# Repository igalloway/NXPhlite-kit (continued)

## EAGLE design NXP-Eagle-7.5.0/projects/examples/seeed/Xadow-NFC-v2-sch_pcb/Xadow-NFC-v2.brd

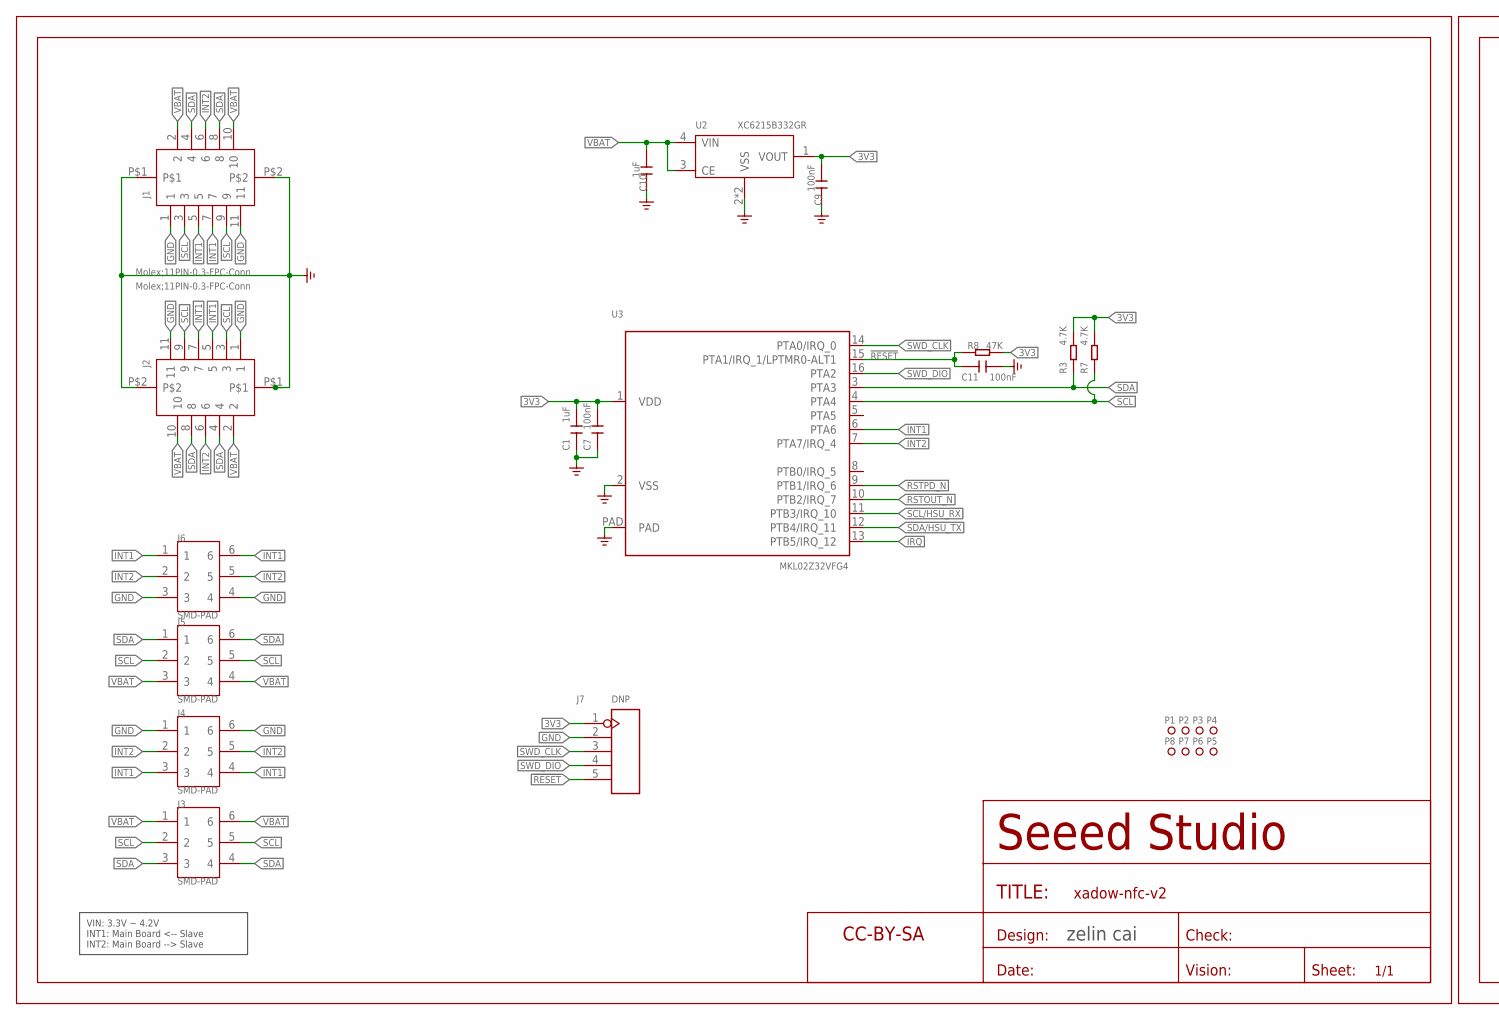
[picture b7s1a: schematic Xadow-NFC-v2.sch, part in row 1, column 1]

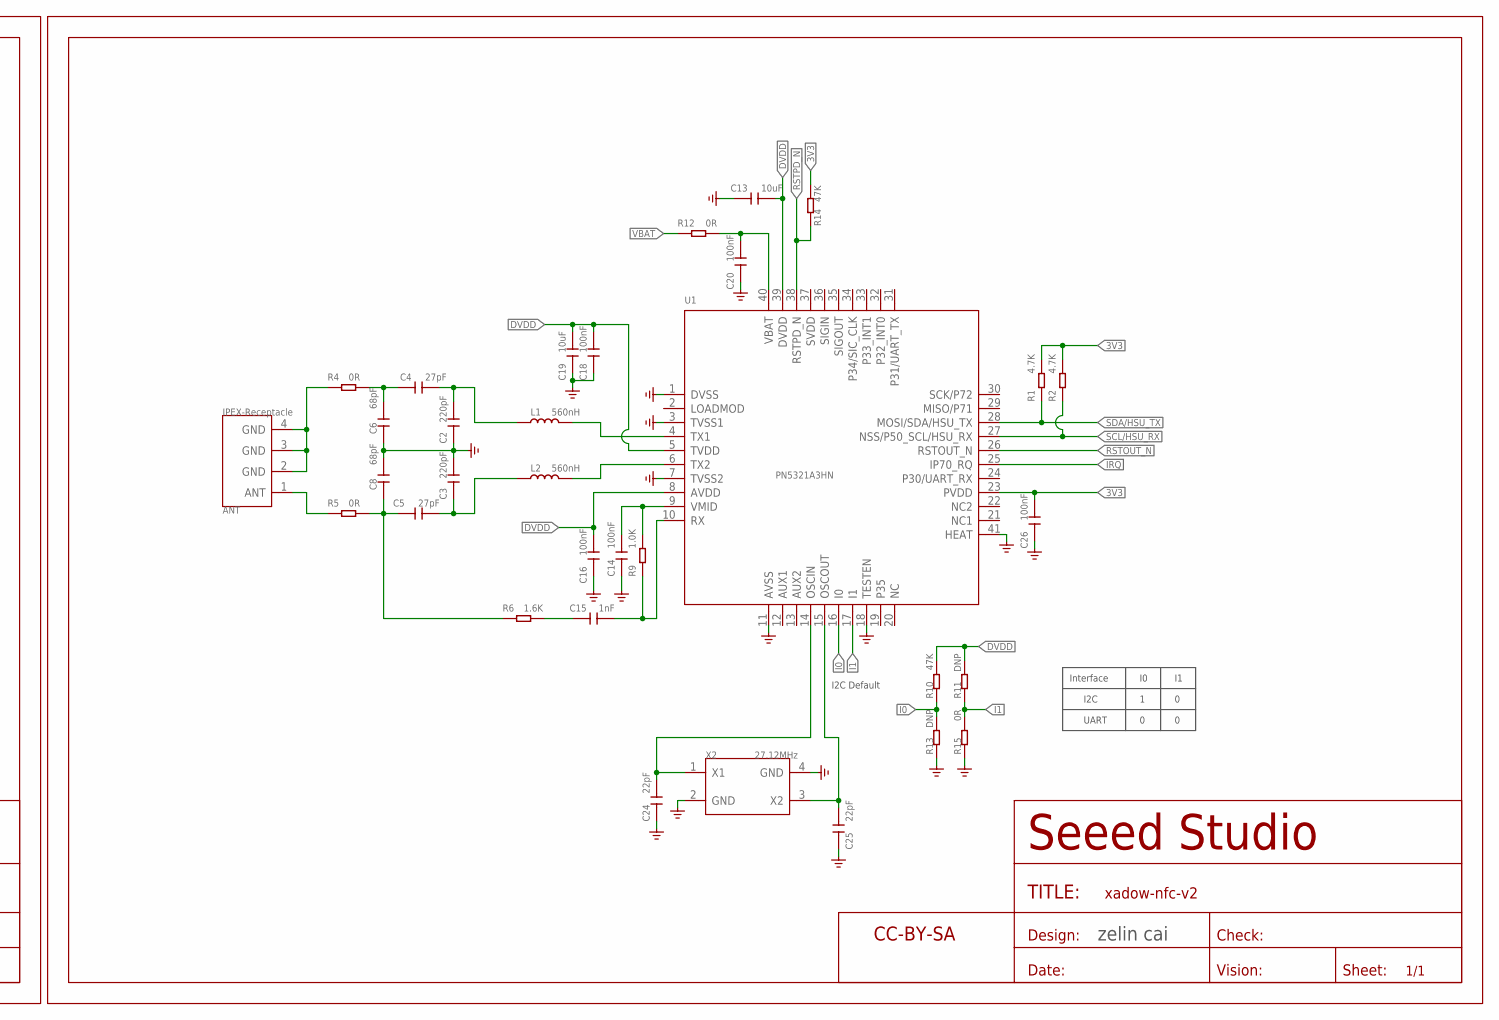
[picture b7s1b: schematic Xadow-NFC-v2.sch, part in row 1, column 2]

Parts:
ANT: IPEX-Receptacle; ANT-IPEX4-1.7X1.7MM
C1, C10: 1uF; C0402
C2, C3: 220pF; C0402
C4, C5: 27pF; C0402
C6, C8: 68pF; C0402
C7, C9, C11, C14, C16, C18, C20, C26: 100nF; C0402
C13, C19: 10uF; C0402
C15: 1nF; C0402
C24, C25: 22pF; C0402
J1, J2: Molex;11PIN-0.3-FPC-Conn; FPC11-SMD-0.3(FH35C)
J3: SMD-PAD; 6P-DIP-2_S3
J4, J6: SMD-PAD; 6P-DIP-2_ROUND
J5: SMD-PAD; 6P-DIP-2
J7: DNP; H5-SMD-2.0-TEST
L1, L2: 560nH; L0603
P1, P2, P3, P4, P5, P6, P7, P8: MRK; ROUND-MARK-1.0
R1, R2, R3, R7: 4.7K; R0402
R4, R5, R12, R15: 0R; R0402
R6: 1.6K; R0402
R8, R10, R14: 47K; R0402
R9: 1.0K; R0402
R11, R13: DNP; R0402
U1: PN5321A3HN; QFN40G-0.5-6X6MM
U2: XC6215B332GR; USP4-0.6-1.2X1.6MM
U3: MKL02Z32VFG4; QFN16G-0.5-3X3MM
U$1: PAGE1; SEEEDSTUDIO-PCB-FRAME
U$21: PAGE2; SEEEDSTUDIO-PCB-FRAME
X2: 27.12MHz; SMD4P-2.0X1.6X0.5MM

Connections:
3V3: C1.2, C7.2, C9.2, C26.2, J7.1, R1.2, R2.2, R3.2, R7.2, R8.2, R14.2, U1.23 (PVDD), U2.1 (VOUT), U3.1 (VDD)
!RESET: C11.1, J7.5, R8.1, U3.15 (PTA1/IRQ_1/LPTMR0-ALT1)
DVDD: C13.1, C16.2, C18.2, C19.2, R10.1, R11.1, U1.5 (TVDD), U1.8 (AVDD), U1.39 (DVDD)
GND: C1.1, C2.1, C3.2, C6.2, C7.1, C8.1, C9.1, C10.1, C11.2, C13.2, C14.1, C16.1, C18.1, C19.1, C20.1, C24.1, C25.1, C26.1, J1.1, J1.11, J1.P$1, J1.P$2, J2.1, J2.11, J2.P$1, J2.P$2, J4.1, J4.6, J6.3, J6.4, J7.2, R13.2, R15.2, U1.1 (DVSS), U1.3 (TVSS1), U1.7 (TVSS2), U1.11 (AVSS), U1.18 (TESTEN), U1.41 (HEAT), U2.2 (VSS), U2.PAD (VSS), U3.2 (VSS), U3.PAD, X2.2 (GND), X2.4 (GND)
I0: R10.2, R13.1, U1.16 (I0)
I1: R11.2, R15.1, U1.17 (I1)
INT1: J1.5, J1.7, J2.5, J2.7, J4.3, J4.4, J6.1, J6.6, U3.6 (PTA6)
INT2: J1.6, J2.6, J4.2, J4.5, J6.2, J6.5, U3.7 (PTA7/IRQ_4)
IRQ: U1.25 (IP70_RQ), U3.13 (PTB5/IRQ_12)
unnamed: C15.1, R9.1, U1.10 (RX)
unnamed: C14.2, R9.2, U1.9 (VMID)
unnamed: C3.1, C5.1, L2.1
unnamed: C2.2, C4.1, L1.1
unnamed: C4.2, C6.1, R4.2
unnamed: C5.2, C8.2, R5.2, R6.1
unnamed: ANT.2 (GND), ANT.3 (GND), ANT.4 (GND), R4.1
unnamed: ANT.1 (ANT), R5.1
unnamed: C15.2, R6.2
unnamed: C24.2, U1.14 (OSCIN), X2.1 (X1)
unnamed: C25.2, U1.15 (OSCOUT), X2.3 (X2)
RSTOUT_N: U1.26 (RSTOUT_N), U3.10 (PTB2/IRQ_7)
RSTPD_N: R14.1, U1.38 (RSTPD_N), U3.9 (PTB1/IRQ_6)
SCL: J1.3, J1.9, J2.3, J2.9, J3.2, J3.5, J5.2, J5.5, R7.1, U3.4 (PTA4)
SCL/HSU_RX: R2.1, U1.27 (NSS/P50_SCL/HSU_RX), U3.11 (PTB3/IRQ_10)
SDA: J1.4, J1.8, J2.4, J2.8, J3.3, J3.4, J5.1, J5.6, R3.1, U3.3 (PTA3)
SDA/HSU_TX: R1.1, U1.28 (MOSI/SDA/HSU_TX), U3.12 (PTB4/IRQ_11)
SWD_CLK: J7.3, U3.14 (PTA0/IRQ_0)
SWD_DIO: J7.4, U3.16 (PTA2)
TX_N: L1.2, U1.4 (TX1)
TX_P: L2.2, U1.6 (TX2)
VBAT: C10.2, C20.2, J1.2, J1.10, J2.2, J2.10, J3.1, J3.6, J5.3, J5.4, R12.1, R12.2, U1.40 (VBAT), U2.3 (CE), U2.4 (VIN)

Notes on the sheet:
zelin cai
VIN: 3.3V ~ 4.2V INT1: Main Board <-- Slave INT2: Main Board --> Slave
Interface
I2C
UART
I2C Default

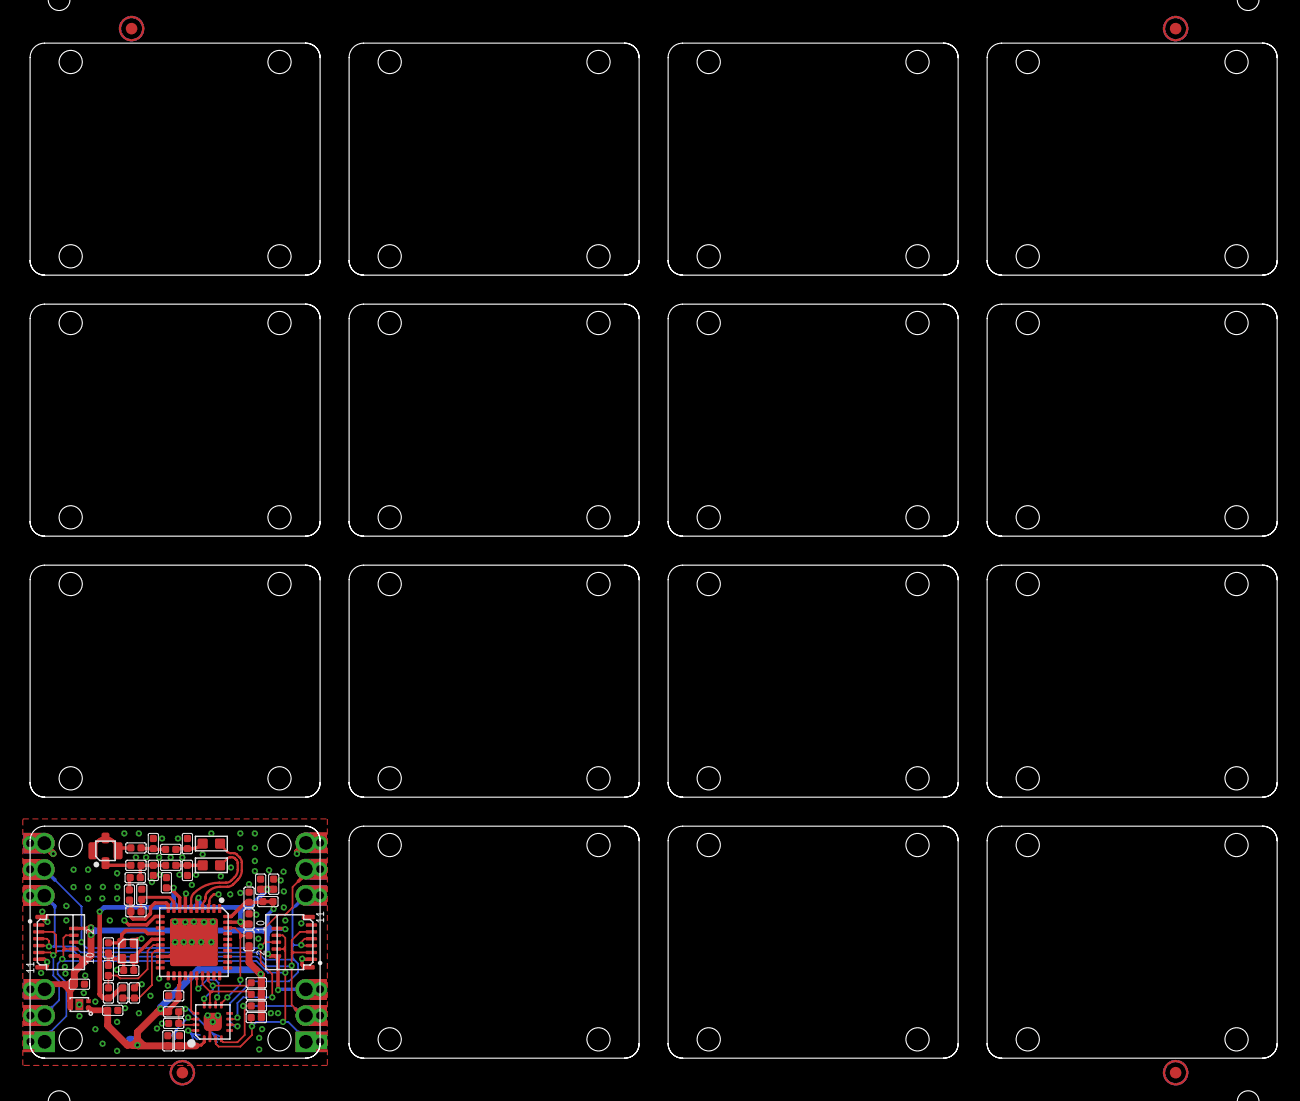
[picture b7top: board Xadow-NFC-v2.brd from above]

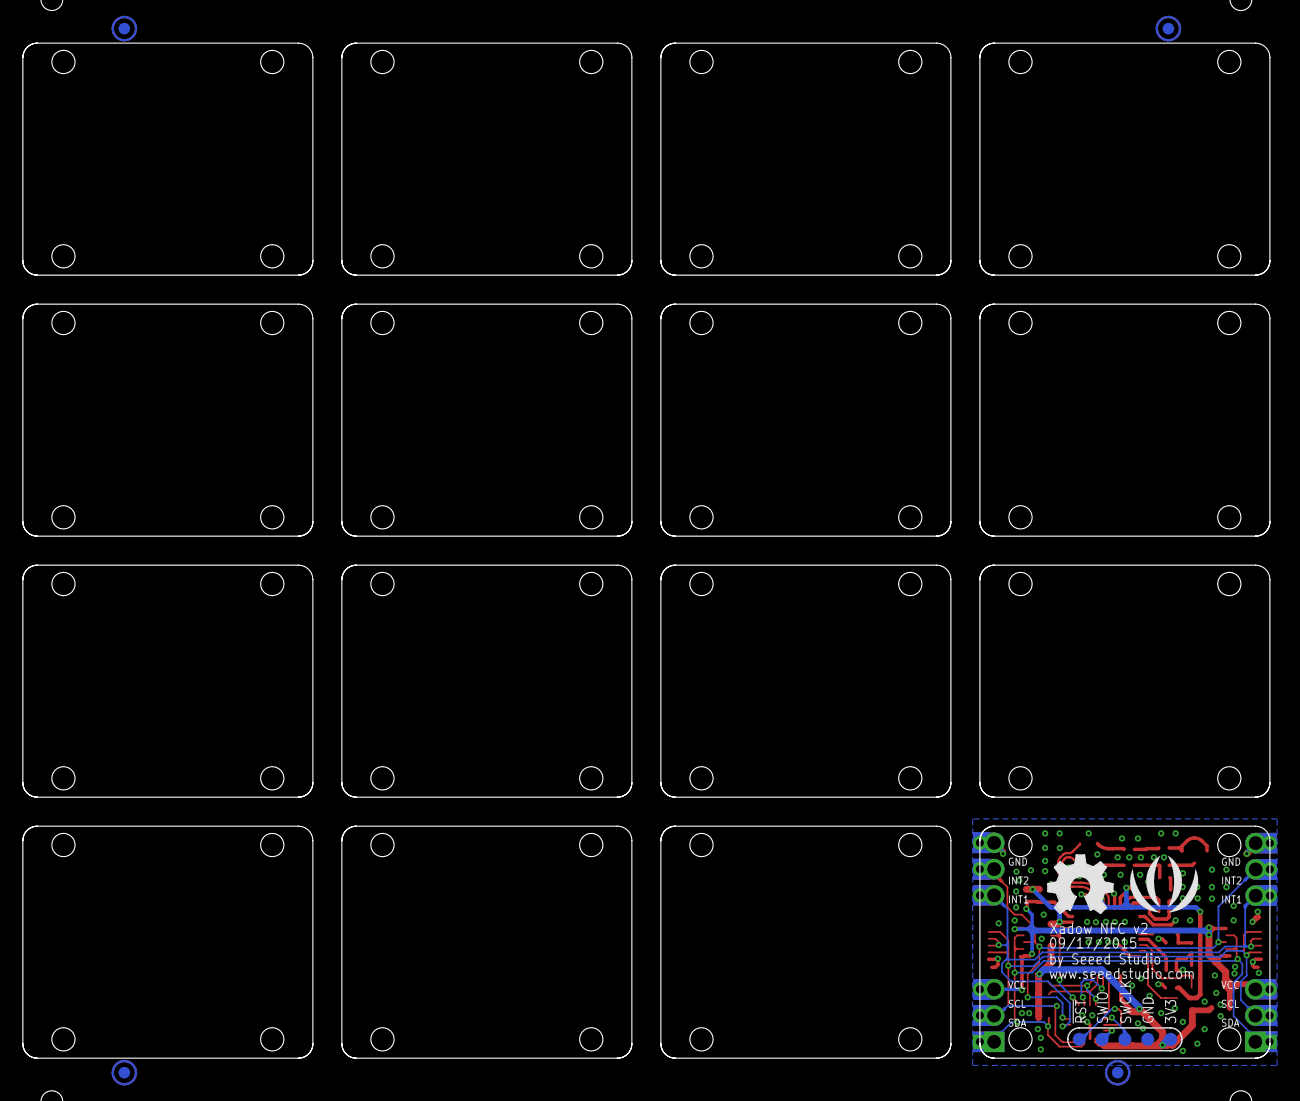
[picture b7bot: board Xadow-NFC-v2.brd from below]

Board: 2 copper layers, 109.2 x 88.9 mm, 62 parts (7 on the bottom side), 31 nets.

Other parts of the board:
U$27: OSHW_FILLX200_NOTEXT
U$29: SEEED-SILK-280*268MIL

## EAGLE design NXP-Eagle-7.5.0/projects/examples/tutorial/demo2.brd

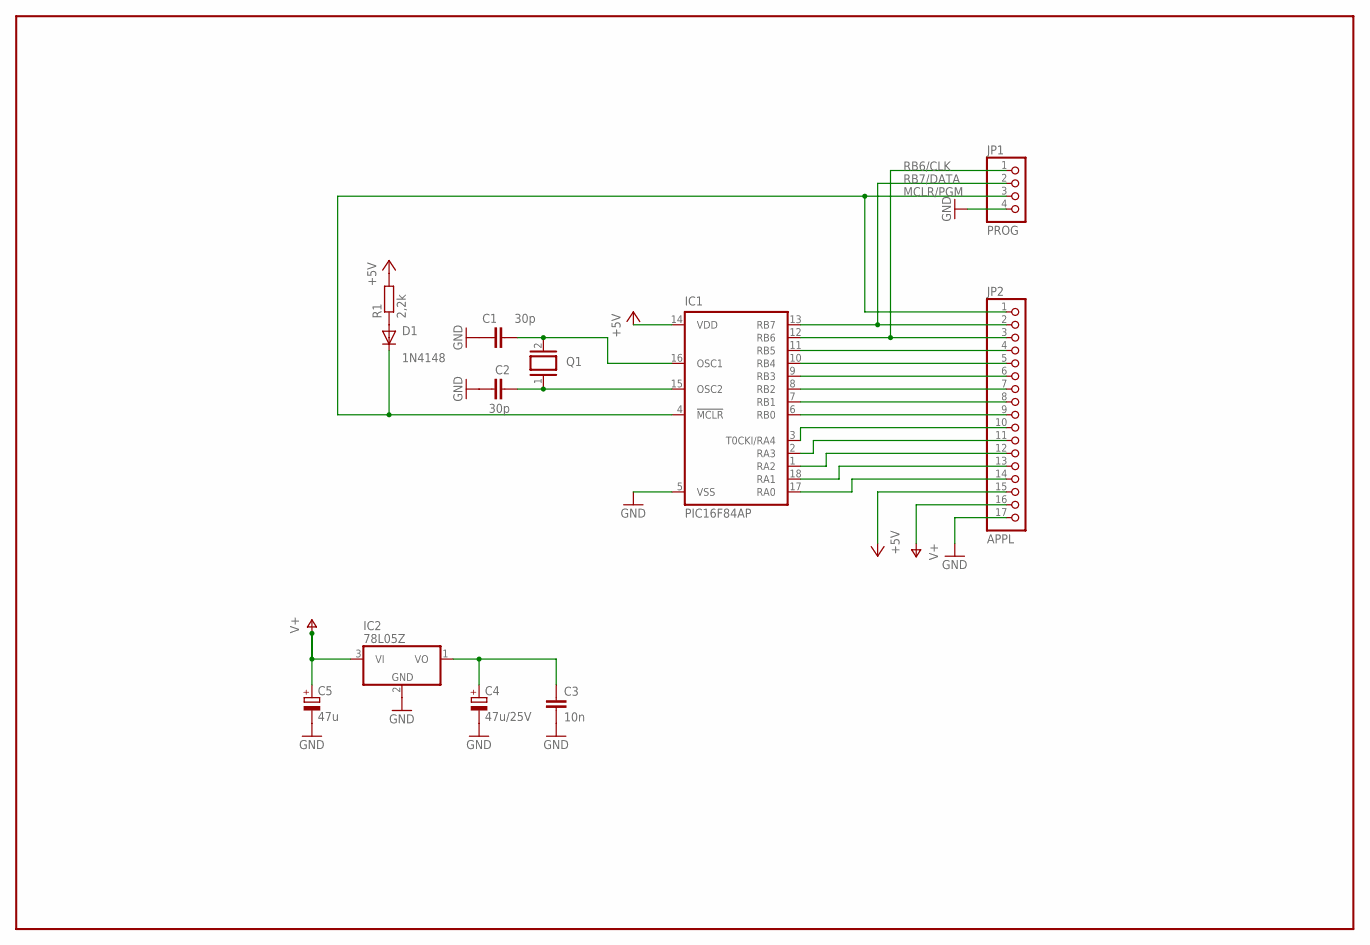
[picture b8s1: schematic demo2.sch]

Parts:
C1, C2: 30p; C1206
C3: 10n; C025-025X050
C4: 47u/25V; TAP5-45
C5: 47u; TAP5-45
D1: 1N4148; DO35-10
IC1: PIC16F84AP; DIL18
IC2: 78L05Z; TO92
JP1: PROG; 1X04
JP2: APPL; 1X17
Q1: XTAL/S; QS
R1: 2,2k; R1206

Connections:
+5V: IC1.14 (VDD), JP2.15, R1.1 (2)
GND: C1.1, C2.1, C3.2, C4.-, C5.-, IC1.5 (VSS), IC2.2 (GND), JP1.4, JP2.17
MCLR/PGM: D1.C, IC1.4 (!MCLR), JP1.3, JP2.1
unnamed: C3.1, C4.+, IC2.1 (VO)
unnamed: C1.2, IC1.16 (OSC1), Q1.2
unnamed: C2.2, IC1.15 (OSC2), Q1.1
unnamed: D1.A, R1.2 (1)
RA0: IC1.17 (RA0), JP2.14
RA1: IC1.18 (RA1), JP2.13
RA2: IC1.1 (RA2), JP2.12
RA3: IC1.2 (RA3), JP2.11
RA4: IC1.3 (T0CKI/RA4), JP2.10
RB0: IC1.6 (RB0), JP2.9
RB1: IC1.7 (RB1), JP2.8
RB2: IC1.8 (RB2), JP2.7
RB3: IC1.9 (RB3), JP2.6
RB4: IC1.10 (RB4), JP2.5
RB5: IC1.11 (RB5), JP2.4
RB6/CLK: IC1.12 (RB6), JP1.1, JP2.3
RB7/DATA: IC1.13 (RB7), JP1.2, JP2.2
V+: C5.+, IC2.3 (VI), JP2.16

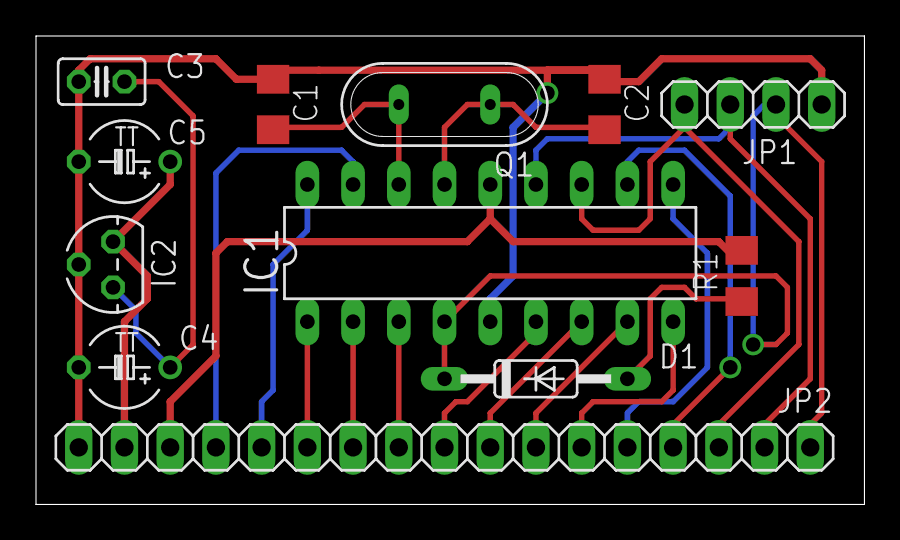
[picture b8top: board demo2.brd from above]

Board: 2 copper layers, 46.0 x 26.0 mm, 12 parts (0 on the bottom side), 21 nets.

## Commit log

2016-06-03 Initial commit (adding eagle base files)
2016-06-06 Adding eagle project stubs for the NXPESC-UF1 and NXPX4
2016-06-06 Create gh-pages branch via GitHub
2016-06-06 Adding original PX4 files from ETH
2016-06-07 Create to-add-to-this-repository
2016-06-08 renaming hardware to NXPhlite-PX4 to avoid confusion with the PX4 Autopilot flight controller software.
2016-06-26 modified description of library sub directory so one can distinguish from default linux installation.
2016-06-26 Removing examples
2016-06-26 Remove NXPX4, to be its own repo
2016-06-26 adding ultralibrarian files
2016-06-26 changed name of project to NXPhlite-kit
2016-06-26 removing extra and unused libraries. These can be found in the initial Eagle installation if you need any.
2016-06-26 Built MKV31F128VLH10.lbr component, tested on NXPESC-UF1/NXPESC-UF1_test.sch
2016-06-26 removing .epf from repository. This file is local to your version of eagle
2016-06-26 Add gitignore
2016-06-26 Add FAN78888 device
2016-06-26 adding FET datsheet Datasheets/PSMN1R4-30YLD.pdf
2016-06-26 Begin sch
2016-06-26 Adding library and datasheet parts
2016-06-26 Changing board name since i was locked out and saveed to NXP-Eagle-7.5.0/projects/NXPESC-UF1/NXPESC-UF1_test002.brd
2016-06-26 Adjusting board part placement too see how things are fitting. will need to compare with what other ESC layouts are like. Presently looking *quite* large!
2016-06-27 lock issue is back. saving now as NXP-Eagle-7.5.0/projects/NXPESC-UF1/NXPESC-UF1_test003.sch
2016-06-27 start of 64pin KV part
2016-06-27 Trial placement on board, Note that the schematic is not complete yet. Also created the 64 pin KV 31 Part.
2016-06-27 Adding the schematics from teh Kinetis KV4 drone reference and also the SBC chip datasheets. Looks initially that the MC33903 (no D/S/P in part number) is the right part for this application.
2016-06-27 superseded by 003 revision
2016-06-27 Adding various can tranceivers that could be useful
2016-06-28 Adding UAVCAN documents for reference
2016-06-28 @gallowaa adding KW40 library part as reference to build KW41 part
2016-06-30 Create TJA1042 and DS
2016-06-30 Working on Layout trying to arrange drivers fets and opamps
2016-06-30 Made TJA1042TK/3 HVSON8 variant
2016-06-30 Add PHY and DF13 4-pin CAN conn to SCH
2016-06-30 update readme re kv31/kv11
2016-07-01 layout continues
2016-07-01 connected additional signals to gate driver
2016-07-02 moved from rev 003 to 004, merged in Gallowaa CAN conenctor additions.
2016-07-03 more test routing. layout is tight but looks possible. Need to switch back to schematic to add missing parts (regulators, connectors, capacitors.)
2016-07-03 Majority of Power FET stage/gate driver and sense amplifiers are layed out. Moving on to finishing the MCU details.
2016-07-14 Minor decriptve updates
2016-07-25 Reviewing NXPESC-UF1/NXPESC-UF1_test004.sch schematic, comparing against SCHEMATICS-FRDM-mc-lvpmsm-sch.pdf
2016-08-10 Draft PDF viewable file for status update
2016-08-15 revisions. Adding MCU components, ESD protection, Thermister, oscillator, RGB LED, checking pinout. Moved CAN interface connection.
2016-08-15 Placing all new parts from schematic update. Looks tricky to fit everything onto this size board. Will likely need to make a bit bigger.
2018-02-28 Set theme jekyll-theme-architect and migrate Page Generator content
